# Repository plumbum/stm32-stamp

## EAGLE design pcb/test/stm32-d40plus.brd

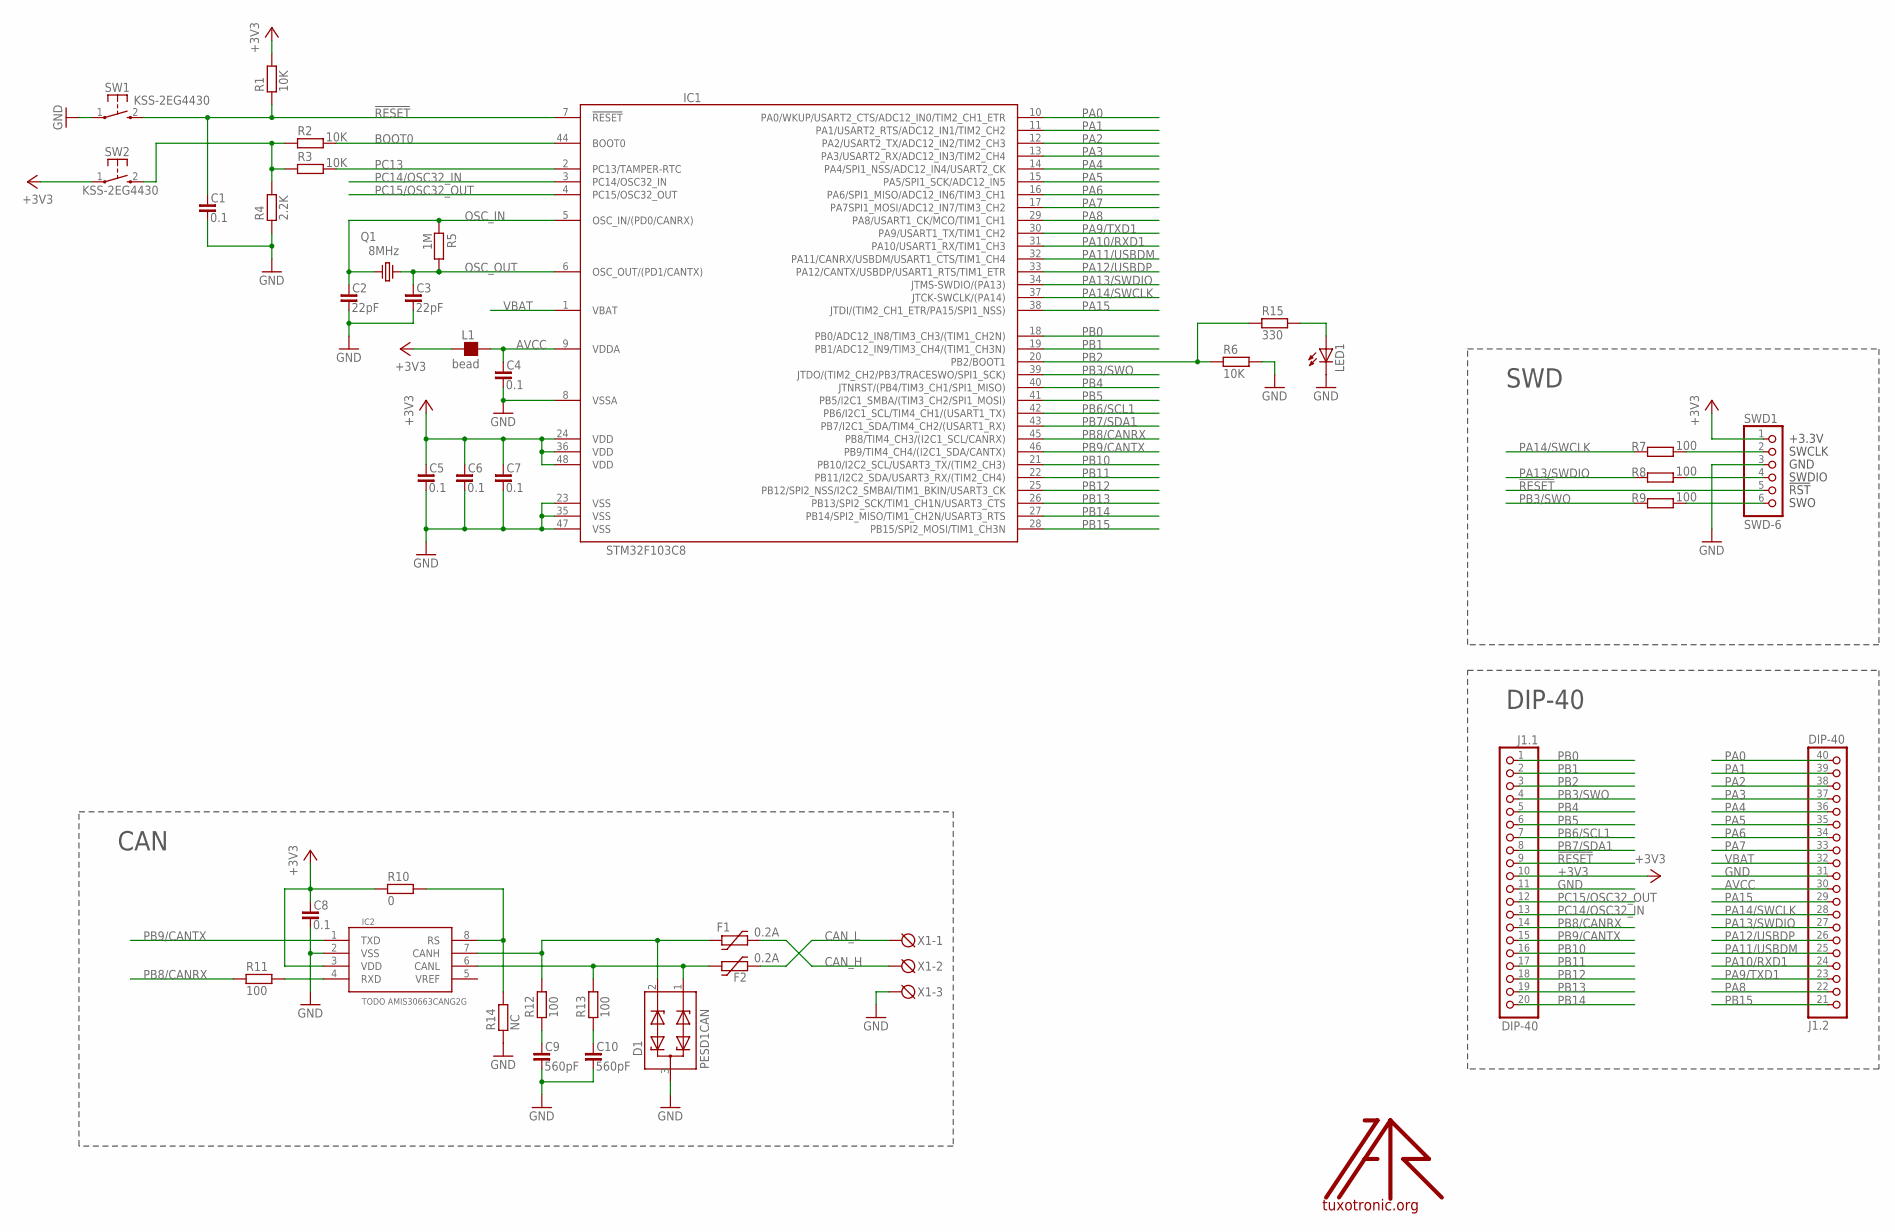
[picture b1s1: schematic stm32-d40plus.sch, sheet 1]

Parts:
C1, C4, C5, C6, C7, C8: 0.1; C0603
C2, C3: 22pF; C0603
C9, C10: 560pF; C0603
D1: PESD1CAN; SOT23
F1, F2: 0.2A; 1206L
IC1: STM32F103C8; LQFP48
IC2: TODO AMIS30663CANG2G; SO08
J1: DIP-40
L1: bead; L0603
LED1: LEDCHIPLED_0603; CHIPLED_0603
Q1: 8MHz; HC49/S
R1, R2, R3, R6: 10K; R0603
R4: 2.2K; R0603
R5: 1M; R0603
R7, R8, R9, R11, R12, R13: 100; R0603
R10: 0; R0603
R14: NC; R0603
R15: 330; R0603
SW1, SW2: KSS-2EG4430
SWD1: SWD-6; JTAG6PIN
U$: LOGO; TT_LOGO
X1: DG3XX-03-3.5; DG350-3.5-03P

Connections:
!RESET: C1.1, IC1.7 (!RESET), J1.9, R1.1, SW1.2 (S), SWD1.5
+3V3: C5.1, C6.1, C7.1, C8.1, IC1.24 (VDD), IC1.36 (VDD), IC1.48 (VDD), IC2.3 (VDD), J1.10, L1.1, R1.2, R10.1, SW2.1, SWD1.1
AVCC: C4.1, IC1.9 (VDDA), J1.30 (10), L1.2
BOOT0: IC1.44 (BOOT0), R2.2
CAN_CTRL: IC2.8 (RS), R10.2, R14.2
CAN_H: F1.P$2 (2), X1.2
CAN_L: F2.P$2 (2), X1.1
GND: C1.2, C2.2, C3.2, C4.2, C5.2, C6.2, C7.2, C8.2, C9.2, C10.2, D1.3, IC1.8 (VSSA), IC1.23 (VSS), IC1.35 (VSS), IC1.47 (VSS), IC2.2 (VSS), J1.11, J1.31 (11), LED1.C, R4.1, R6.2, R14.1, SW1.1, SWD1.3, X1.3
unnamed: R2.1, R3.1, R4.2, SW2.2 (S)
unnamed: R7.2, SWD1.2
unnamed: R8.2, SWD1.4
unnamed: R9.2, SWD1.6
unnamed: LED1.A, R15.2
unnamed: IC2.4 (RXD), R11.2
unnamed: D1.2, F1.P$1 (1), IC2.7 (CANH), R12.2
unnamed: D1.1, F2.P$1 (1), IC2.6 (CANL), R13.2
unnamed: C10.1, R13.1
unnamed: C9.1, R12.1
OSC_IN: C2.1, IC1.5 (OSC_IN/(PD0/CANRX)), Q1.1, R5.1
OSC_OUT: C3.1, IC1.6 (OSC_OUT/(PD1/CANTX)), Q1.2, R5.2
PA0: IC1.10 (PA0/WKUP/USART2_CTS/ADC12_IN0/TIM2_CH1_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), J1.40 (20)
PA1: IC1.11 (PA1/USART2_RTS/ADC12_IN1/TIM2_CH2), J1.39 (19)
PA2: IC1.12 (PA2/USART2_TX/ADC12_IN2/TIM2_CH3), J1.38 (18)
PA3: IC1.13 (PA3/USART2_RX/ADC12_IN3/TIM2_CH4), J1.37 (17)
PA4: IC1.14 (PA4/SPI1_NSS/ADC12_IN4/USART2_CK), J1.36 (16)
PA5: IC1.15 (PA5/SPI1_SCK/ADC12_IN5), J1.35 (15)
PA6: IC1.16 (PA6/SPI1_MISO/ADC12_IN6/TIM3_CH1), J1.34 (14)
PA7: IC1.17 (PA7SPI1_MOSI/ADC12_IN7/TIM3_CH2), J1.33 (13)
PA8: IC1.29 (PA8/USART1_CK/MCO/TIM1_CH1), J1.22 (2)
PA9/TXD1: IC1.30 (PA9/USART1_TX/TIM1_CH2), J1.23 (3)
PA10/RXD1: IC1.31 (PA10/USART1_RX/TIM1_CH3), J1.24 (4)
PA11/USBDM: IC1.32 (PA11/CANRX/USBDM/USART1_CTS/TIM1_CH4), J1.25 (5)
PA12/USBDP: IC1.33 (PA12/CANTX/USBDP/USART1_RTS/TIM1_ETR), J1.26 (6)
PA13/SWDIO: IC1.34 (JTMS-SWDIO/(PA13)), J1.27 (7), R8.1
PA14/SWCLK: IC1.37 (JTCK-SWCLK/(PA14)), J1.28 (8), R7.1
PA15: IC1.38 (JTDI/(TIM2_CH1_ETR/PA15/SPI1_NSS)), J1.29 (9)
PB0: IC1.18 (PB0/ADC12_IN8/TIM3_CH3/(TIM1_CH2N)), J1.1
PB1: IC1.19 (PB1/ADC12_IN9/TIM3_CH4/(TIM1_CH3N)), J1.2
PB2: IC1.20 (PB2/BOOT1), J1.3, R6.1, R15.1
PB3/SWO: IC1.39 (JTDO/(TIM2_CH2/PB3/TRACESWO/SPI1_SCK)), J1.4, R9.1
PB4: IC1.40 (JTNRST/(PB4/TIM3_CH1/SPI1_MISO)), J1.5
PB5: IC1.41 (PB5/I2C1_SMBA/(TIM3_CH2/SPI1_MOSI)), J1.6
PB6/SCL1: IC1.42 (PB6/I2C1_SCL/TIM4_CH1/(USART1_TX)), J1.7
PB7/SDA1: IC1.43 (PB7/I2C1_SDA/TIM4_CH2/(USART1_RX)), J1.8
PB8/CANRX: IC1.45 (PB8/TIM4_CH3/(I2C1_SCL/CANRX)), J1.14, R11.1
PB9/CANTX: IC1.46 (PB9/TIM4_CH4/(I2C1_SDA/CANTX)), IC2.1 (TXD), J1.15
PB10: IC1.21 (PB10/I2C2_SCL/USART3_TX/(TIM2_CH3)), J1.16
PB11: IC1.22 (PB11/I2C2_SDA/USART3_RX/(TIM2_CH4)), J1.17
PB12: IC1.25 (PB12/SPI2_NSS/I2C2_SMBAI/TIM1_BKIN/USAR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), J1.18
PB13: IC1.26 (PB13/SPI2_SCK/TIM1_CH1N/USART3_CTS), J1.19
PB14: IC1.27 (PB14/SPI2_MISO/TIM1_CH2N/USART3_RTS), J1.20
PB15: IC1.28 (PB15/SPI2_MOSI/TIM1_CH3N), J1.21 (1)
PC13: IC1.2 (PC13/TAMPER-RTC), R3.2
PC14/OSC32_IN: IC1.3 (PC14/OSC32_IN), J1.13
PC15/OSC32_OUT: IC1.4 (PC15/OSC32_OUT), J1.12
VBAT: IC1.1 (VBAT), J1.32 (12)

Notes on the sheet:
CAN
DIP-40
SWD

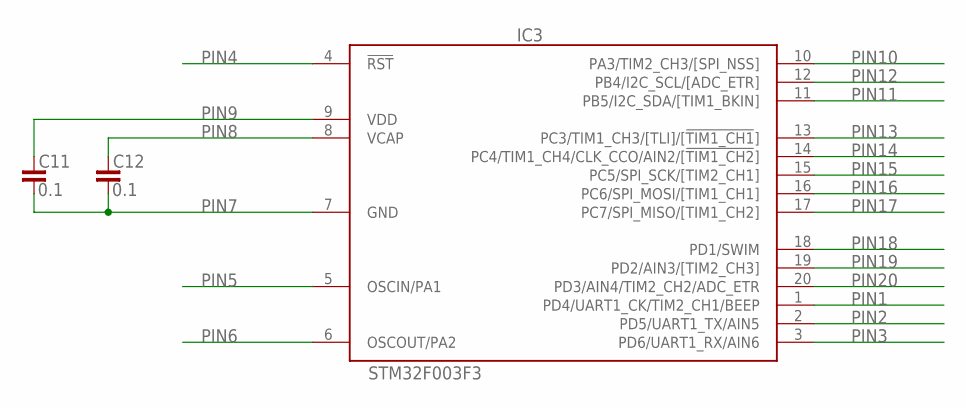
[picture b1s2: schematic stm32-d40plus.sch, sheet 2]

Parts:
C11, C12: 0.1; C0805
IC3: STM32F003F3; TSSOP20

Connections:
PIN1: IC3.1 (PD4/UART1_CK/TIM2_CH1/BEEP)
PIN2: IC3.2 (PD5/UART1_TX/AIN5)
PIN3: IC3.3 (PD6/UART1_RX/AIN6)
PIN4: IC3.4 (!RST)
PIN5: IC3.5 (OSCIN/PA1)
PIN6: IC3.6 (OSCOUT/PA2)
PIN7: C11.2, C12.2, IC3.7 (GND)
PIN8: C12.1, IC3.8 (VCAP)
PIN9: C11.1, IC3.9 (VDD)
PIN10: IC3.10 (PA3/TIM2_CH3/[SPI_NSS])
PIN11: IC3.11 (PB5/I2C_SDA/[TIM1_BKIN])
PIN12: IC3.12 (PB4/I2C_SCL/[ADC_ETR])
PIN13: IC3.13 (PC3/TIM1_CH3/[TLI]/[!TIM1_CH1!])
PIN14: IC3.14 (PC4/TIM1_CH4/CLK_CCO/AIN2/[!TIM1_CH2!])
PIN15: IC3.15 (PC5/SPI_SCK/[TIM2_CH1])
PIN16: IC3.16 (PC6/SPI_MOSI/[TIM1_CH1])
PIN17: IC3.17 (PC7/SPI_MISO/[TIM1_CH2])
PIN18: IC3.18 (PD1/SWIM)
PIN19: IC3.19 (PD2/AIN3/[TIM2_CH3])
PIN20: IC3.20 (PD3/AIN4/TIM2_CH2/ADC_ETR)

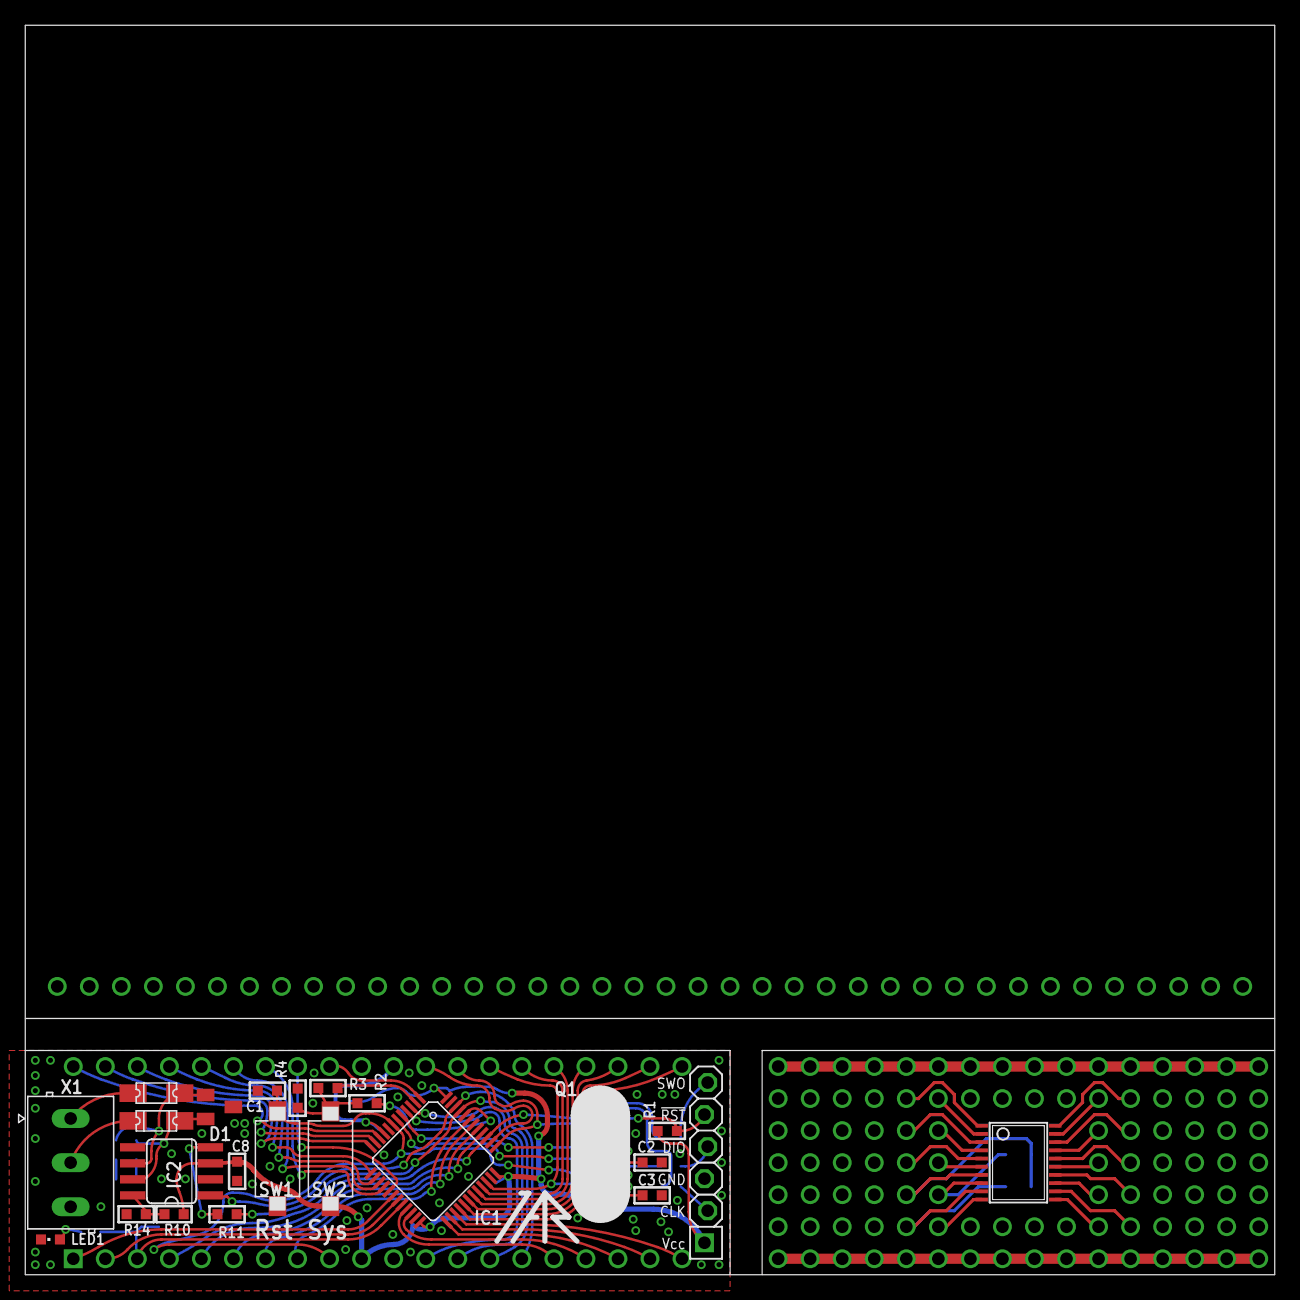
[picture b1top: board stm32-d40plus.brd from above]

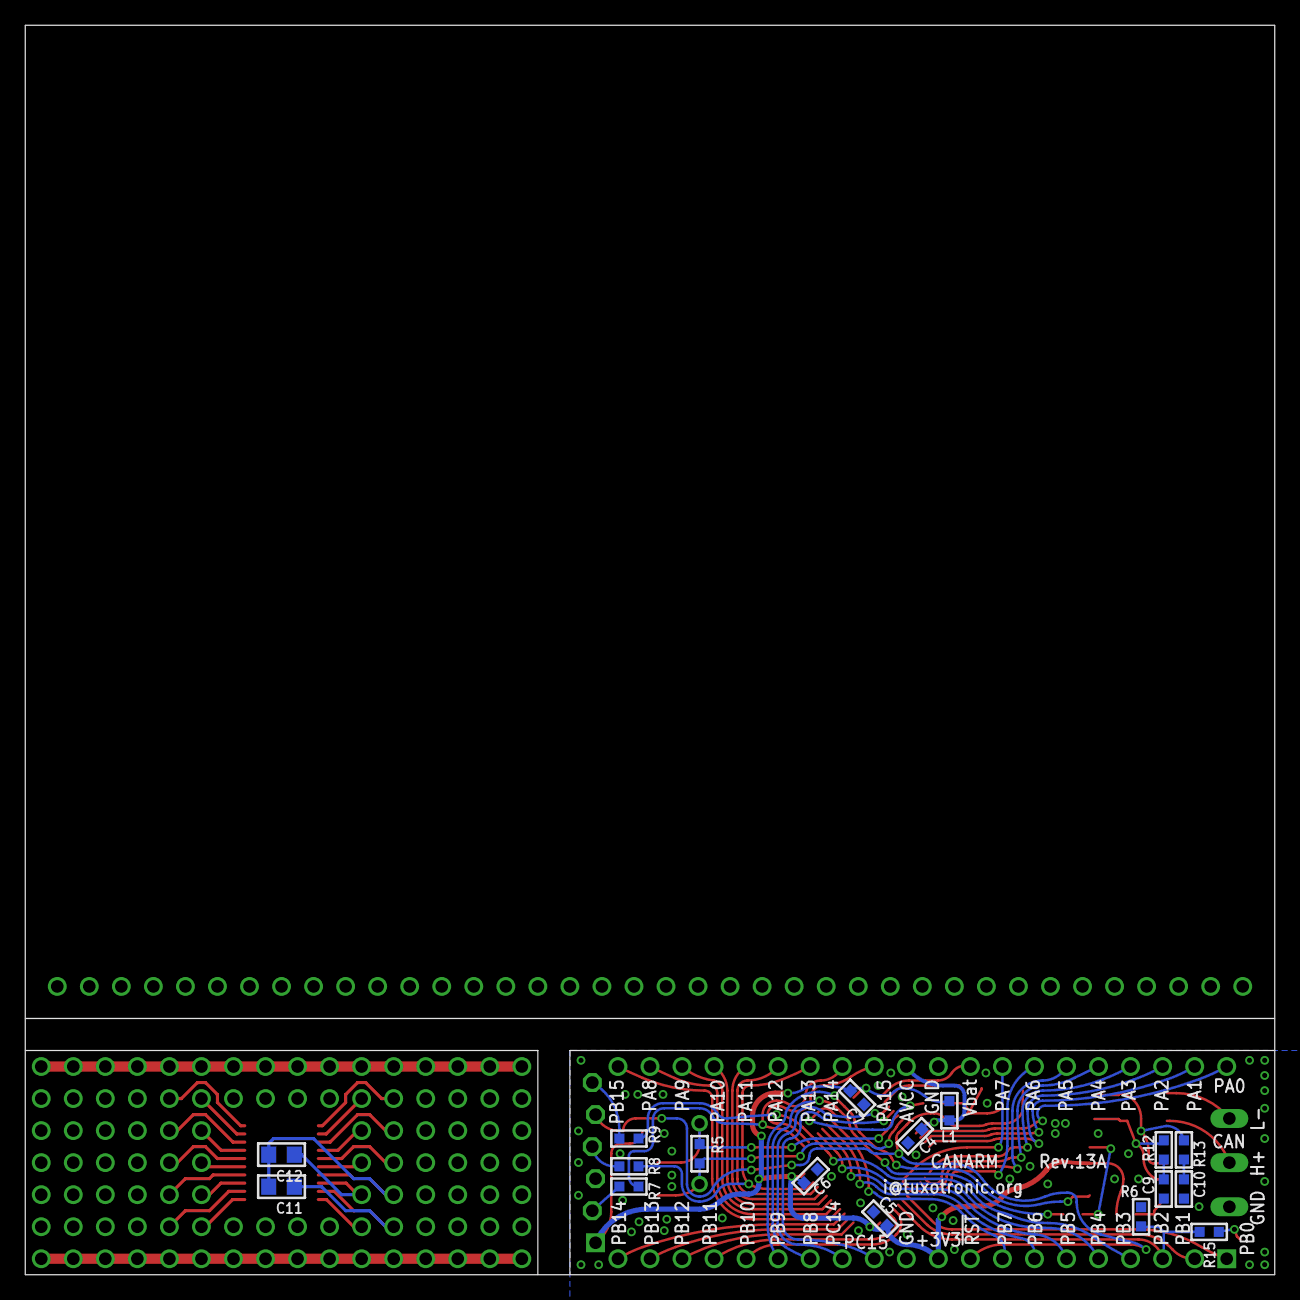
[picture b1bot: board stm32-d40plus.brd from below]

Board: 2 copper layers, 99.1 x 99.1 mm, 42 parts (17 on the bottom side), 59 nets.

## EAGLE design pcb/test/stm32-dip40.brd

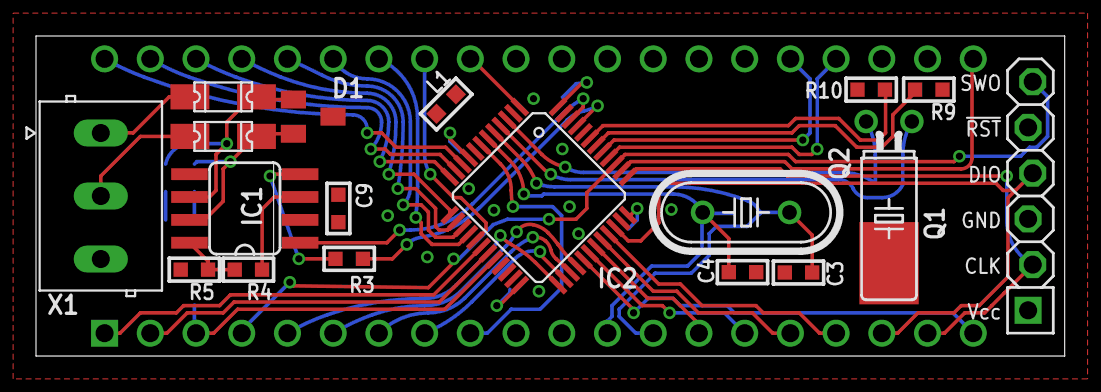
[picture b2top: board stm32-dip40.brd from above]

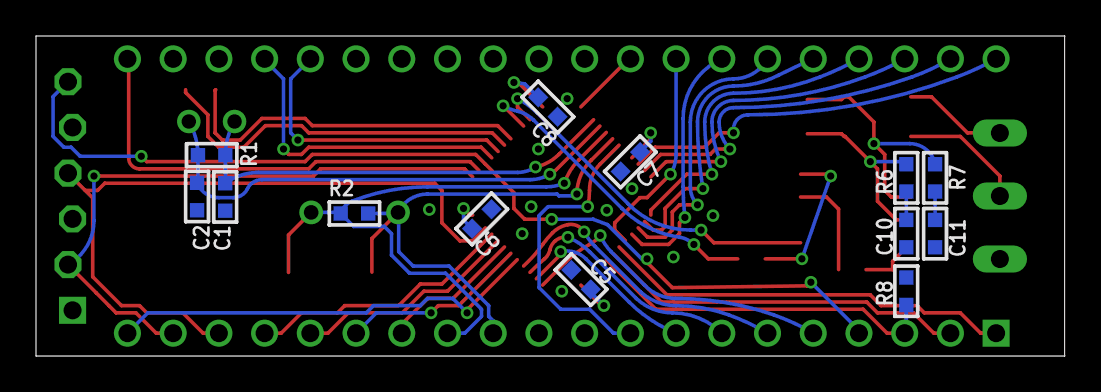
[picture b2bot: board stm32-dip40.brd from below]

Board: 2 copper layers, 57.1 x 17.8 mm, 32 parts (13 on the bottom side), 47 nets.

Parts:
C1, C2: 10pF; C0603
C3, C4: 22pF; C0603
C5, C6, C7, C8, C9: 0.1; C0603
C10, C11: 560pF; C0603
D1: PESD1CAN; SOT23
F1, F2: 0.2A; 1206L
IC1: TODO AMIS30663CANG2G; SO08
IC2: STM32F103C8; LQFP48
J1: DIP-40
L1: bead; L0603
Q1: 32768Hz; TC38H-G
Q2: 8MHz; HC49/S
R1, R2: 1M; R0603
R3, R6, R7: 100; R0603
R4: 0; R0603
R5: NC; R0603
R8, R9, R10: 10K; R0603
SWD1: SWD-6; JTAG6PIN
X1: DG3XX-03-3.5; DG350-3.5-03P

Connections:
!RESET: IC2.7, J1.9, SWD1.5
+3V3: C5.1, C6.1, C8.1, C9.1, IC1.3, IC2.24, IC2.36, IC2.48, J1.10, L1.1, R4.1, R9.2, R10.2, SWD1.1
AVCC: C7.1, IC2.9, J1.30, L1.2
CAN_CTRL: IC1.8, R4.2, R5.2
CAN_H: F1.P$2, X1.2
CAN_L: F2.P$2, X1.1
CAN_RX: IC2.45, R3.1
CAN_TX: IC1.1, IC2.46
GND: C1.2, C2.2, C3.2, C4.2, C5.2, C6.2, C7.2, C8.2, C9.2, C10.2, C11.2, D1.3, IC1.2, IC2.8, IC2.23, IC2.35, IC2.47, J1.11, J1.31, R5.1, R8.2, SWD1.3, X1.3
I2C1_SCL: IC2.42, J1.22, R9.1
I2C1_SDA: IC2.43, J1.23, R10.1
unnamed: IC1.4, R3.2
unnamed: D1.2, F1.P$1, IC1.7, R6.2
unnamed: D1.1, F2.P$1, IC1.6, R7.2
unnamed: C11.1, R7.1
unnamed: C10.1, R6.1
OSC32_IN: C1.1, IC2.3, Q1.2, R1.1
OSC32_OUT: C2.1, IC2.4, Q1.1, R1.2
PA0: IC2.10, J1.40
PA1: IC2.11, J1.39
PA2: IC2.12, J1.38
PA3: IC2.13, J1.37
PA4: IC2.14, J1.36
PA5: IC2.15, J1.35
PA6: IC2.16, J1.34
PA7: IC2.17, J1.33
PA8: IC2.29, J1.20
PA15: IC2.38, J1.21
PB0: IC2.18, J1.1
PB1: IC2.19, J1.2
PB2: IC2.20, J1.3, R8.1
PB3/SWO: IC2.39, J1.4, SWD1.6
PB4: IC2.40, J1.24
PB5: IC2.41, J1.25
RXD1: IC2.31, J1.14
SPI2_MISO: IC2.27, J1.7
SPI2_MOSI: IC2.28, J1.6
SPI2_NSS: IC2.25, J1.5
SPI2_SCK: IC2.26, J1.8
SWCLK: IC2.37, J1.19, SWD1.2
SWDIO: IC2.34, J1.18, SWD1.4
TXD1: IC2.30, J1.15
USBDM: IC2.32, J1.16
USBDP: IC2.33, J1.17
VBAT: IC2.1, J1.32
XTAL1: C3.1, IC2.5, J1.13, Q2.1, R2.1
XTAL2: C4.1, IC2.6, J1.12, Q2.2, R2.2
